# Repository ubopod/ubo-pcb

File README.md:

# Ubo PCBs

Open hardware design files for the printed circuit boards in the [Ubo Pod](https://getubo.com)
and its accessories — the main Raspberry Pi HAT, the side connector board, PCIe and M.2
adapters, a flex cable, and an NFC board. Sources are a mix of **Eagle CAD** and **KiCad**;
newer designs are KiCad.

<table>
  <tr>
    <td align="center" width="33%">
      <br>
      <sub><b><a href="boards/ubo-sideboard/">Sideboard</a></b><br>ports to the back panel</sub>
    </td>
    <td align="center" width="33%">
      <br>
      <sub><b><a href="boards/ubo-hab-v2/">HAB v2</a></b><br>PCIe, USB-C PD and PoE+</sub>
    </td>
    <td align="center" width="33%">
      <br>
      <sub><b><a href="boards/ubo-pcie-adapter/">PCIe adapter</a></b><br>M.2 M-key for the Pi 5</sub>
    </td>
  </tr>
  <tr>
    <td align="center">
      <br>
      <sub><b><a href="boards/m2-mkey-to-aekey/">M.2 M-key to A/E-key</a></b><br>runs a Google Coral</sub>
    </td>
    <td align="center">
      <br>
      <sub><b><a href="boards/pcie-fpc-s-shaped/">S-shaped PCIe FPC</a></b><br>2-layer flex cable</sub>
    </td>
    <td align="center">
      <br>
      <sub><b>As fabricated</b><br>a populated sideboard</sub>
    </td>
  </tr>
</table>

## Boards

Each board lives in its own directory under [`boards/`](boards/) with its own README.

| Board | Rev | Tool | Status | Connects to |
|---|---|---|---|---|
| [**ubo-top-hat**](boards/ubo-top-hat/) | v1.6 | Eagle | Production | Raspberry Pi 40-pin header |
| [**ubo-sideboard**](boards/ubo-sideboard/) | v1.5.2 | KiCad | Current | Pi 4/5 side ports + top HAT |
| ↳ [v1.4](boards/ubo-sideboard/v1.4-eagle/) | v1.4 | Eagle | Superseded by v1.5.2 | — |
| [**ubo-hab-v2**](boards/ubo-hab-v2/) | v4 | KiCad | Current | Raspberry Pi 5 PCIe + power |
| [**ubo-pcie-adapter**](boards/ubo-pcie-adapter/) | v3 | KiCad | Superseded by HAB v2 | Raspberry Pi 5 PCIe |
| [**m2-mkey-to-aekey**](boards/m2-mkey-to-aekey/) | — | KiCad | Built and tested | M.2 M-key slot |
| [**pcie-fpc-s-shaped**](boards/pcie-fpc-s-shaped/) | v2 | KiCad | Prototype, revision in progress | PCIe adapter FPC connectors |
| [**ubo-nfc-hat**](boards/ubo-nfc-hat/) | 1.0 | KiCad | Experimental | I²C via 1×8 headers |

**What each one is:**

- **ubo-top-hat** — the main Ubo board. LCD, keypad, RGB LED ring, WM8960 audio with speakers and
  microphones, IR transmit/receive, temperature and light sensors, EEPROM, fan, power button, and
  an experimental SDR section.
- **ubo-sideboard** — brings the Pi's mini HDMI, USB-C power, and audio jack around to the back of
  the enclosure, and adds a microSD extender, STEMMA Qt connectors, a power button, and a fan header.
- **ubo-hab-v2** — "hardware added on the bottom." PCIe to M.2 M-key, with optional USB-C PD and
  PoE+ power input modules and 12V/5V/3.3V breakouts.
- **ubo-pcie-adapter** — the first HAB revision; a simpler PCIe to M.2 M-key adapter.
- **m2-mkey-to-aekey** — adapts an M.2 M-key slot to A/E-key, so a Google Coral accelerator can go
  where an NVMe drive would.
- **pcie-fpc-s-shaped** — a 2-layer S-shaped FPC cable matching the connector positions on the
  PCIe adapter.
- **ubo-nfc-hat** — NTAG I²C plus NFC tag with a chain of addressable RGB LEDs.

## Repository layout

One directory per board. Within a board directory:

```
boards/<board>/
  README.md          documentation for this board
  <design files>     KiCad project or Eagle .sch/.brd at the top level,
                     or in a <rev>-<tool>/ subdirectory when a board has
                     more than one revision (see ubo-sideboard)
  images/            renders, layout screenshots, photos
  docs/              exported schematic and assembly PDFs
  datasheets/        datasheets for the components used on this board
  mechanical/        board outline DXF, STEP and other 3D models
```

Not every board has every subdirectory — they exist where there is something to put in them.

## Opening the files

- **KiCad projects** (`.kicad_pro`) — KiCad 8 or 9. Open the `.kicad_pro`, not the individual
  schematic or board files, so the project's library tables load.
- **Eagle designs** (`.sch` / `.brd`) — authored in Eagle CAD 9.6.2. KiCad can also import them
  via *File → Import → Non-KiCad Project*.

## License

Copyright © Ubo Pod.

These designs are licensed under the **CERN Open Hardware Licence Version 2 – Strongly
Reciprocal** (`CERN-OHL-S-2.0`). The full text is in [LICENSE](LICENSE).

In plain terms:

- **You can** use, study, modify, manufacture, and sell these boards, commercially or not.
- **If you distribute a modified design**, you have to release your modified source under this
  same licence, so the next person gets what you got.
- **If you sell or give away a product** made from these designs, you have to tell the recipient
  where to obtain the source for it.
- **There is no warranty.** These are hobbyist and small-batch designs; verify them yourself
  before committing to a fabrication run.

That summary is for orientation only — [LICENSE](LICENSE) is the document that actually governs.

To reuse a board here, keep the copyright and licence notices in the design files, and note your
own changes.

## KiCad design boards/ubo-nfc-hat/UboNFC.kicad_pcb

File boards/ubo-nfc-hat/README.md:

# Ubo NFC Hat

An NFC tag board with an addressable RGB LED ring, designed to attach to the Ubo Pod over I²C.
See the [repository index](../../README.md) for the other boards.

| | |
|---|---|
| **Revision** | 1.0 (schematic title block dated 2024-09-15) |
| **Tool** | KiCad — `UboNFC.kicad_pro` |
| **Stack-up** | 2 layers (F.Cu / B.Cu) |
| **Interface** | I²C + 1-wire LED data, via a pair of 1×8 headers |

## Attribution

This design is derived from **"Badge Tag NFC" by HXR.DK**, which is still named in the KiCad
schematic title block. The Ubo adaptation keeps the upstream NFC front-end and adds the LED
chain and the pass-through header arrangement described below.

> **TODO:** confirm the upstream project URL and its license, and record both here.

## Design

| Part | Function |
|---|---|
| **NXP NT3H2x11** (NTAG I²C plus) | NFC Forum Type 2 tag with an I²C interface, password protection, and energy harvesting. Readable by a phone over NFC *and* by the host over I²C. |
| **12 × SK6812SIDE-A** | Side-firing addressable RGB LEDs, daisy-chained from `LED_IN` through to `LED_OUT`. |
| **3 × SD103AW** | Schottky diodes on the LED data / signal lines. |
| **R1–R3, C1** | Pull-ups and decoupling. |

Named nets of interest: `COIL` and `VOUT` are the NFC antenna coil and the energy-harvesting
output; `FieldDetect` signals the host when an NFC field is present; `PushButton` brings a
button input out to the headers.

## Pinout

Two 1×8 horizontal headers. **J1** is the input side and **J2** carries the same signals back out
plus `LED_OUT`, so the LED chain and the I²C bus can be continued to a downstream board.

| Pin | J1 (in) | J2 (out) |
|---:|---|---|
| 1 | +5V | LED_OUT |
| 2 | +3V3 | PushButton |
| 3 | SDA | GND |
| 4 | SCL | GND |
| 5 | LED_IN | SCL |
| 6 | GND | SDA |
| 7 | FieldDetect | +3V3 |
| 8 | PushButton | +5V |

Note that J2 is **not** a straight-through mirror of J1 — the pin order differs. Check the
orientation of any cable you build against this table.

## Status

Experimental. There are no board renders, photos, or fabrication outputs in the repo yet, and
the design has not been documented as built or tested.

> **TODO:** confirm which Ubo board or connector J1 is intended to mate with, and whether the
> `FieldDetect` and `PushButton` lines are wired to specific host GPIOs.

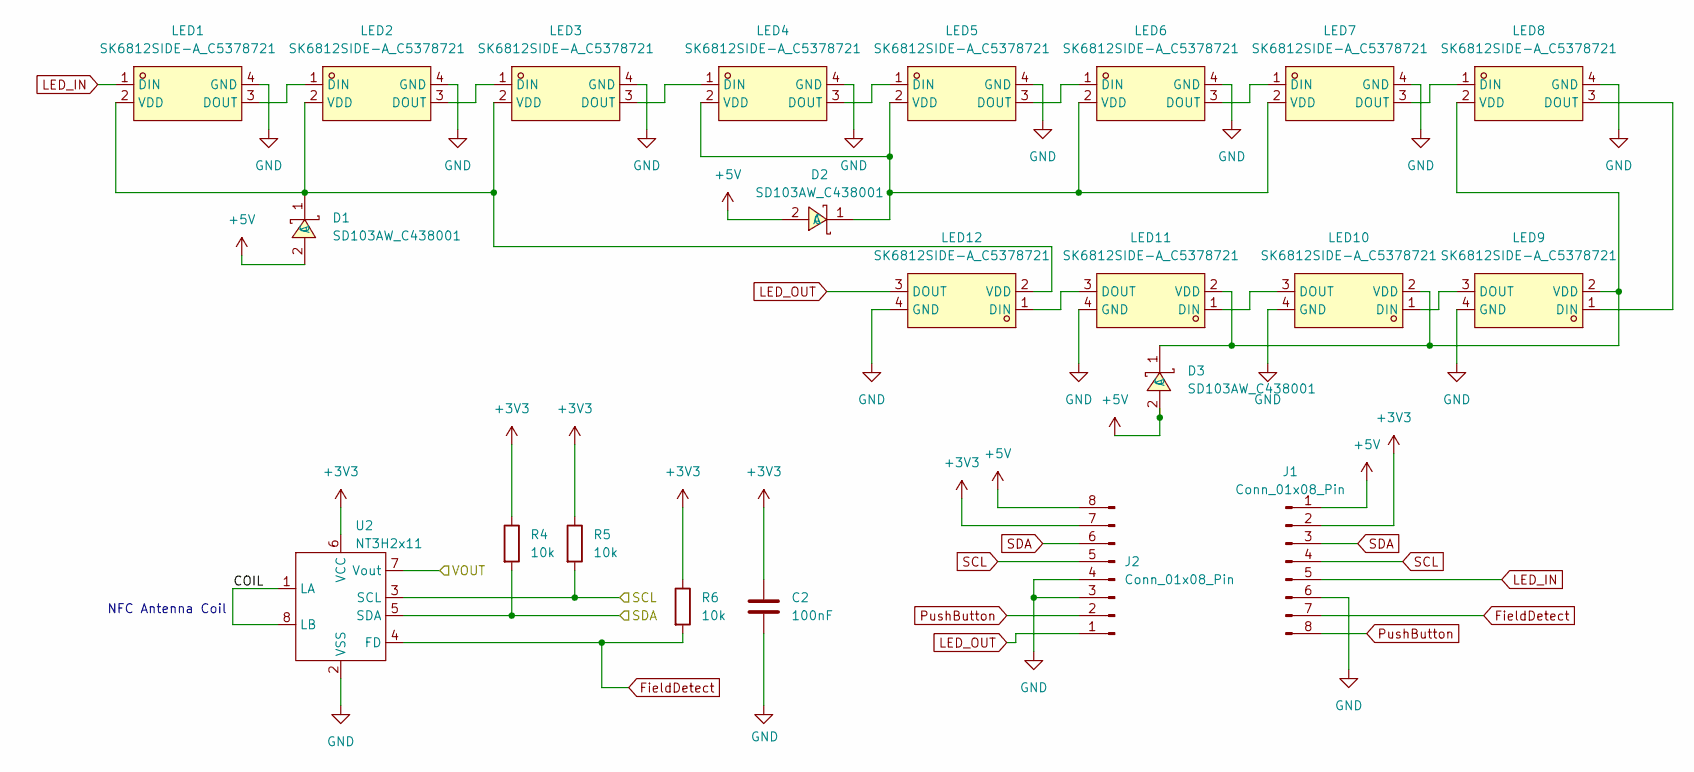
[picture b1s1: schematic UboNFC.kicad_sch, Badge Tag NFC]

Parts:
C2: 100nF; C_0603_1608Metric; LCSC C14663
D1, D2, D3: SD103AW_C438001; SOD-123_L2.7-W1.6-LS3.7-RD; LCSC Part C438001
J1, J2: Conn_01x08_Pin; PinHeader_1x08_P2.54mm_Horizontal
LED1, LED2, LED3, LED4, LED5, LED6, LED7, LED8, LED9, LED10, LED11, LED12: SK6812SIDE-A_C5378721; LED-SMD_4P-L4.0-W1.6-L; LCSC Part C5378721
R4, R5, R6: 10k; R_0603_1608Metric; LCSC C25804
U2: NT3H2x11; SO-8_3.9x4.9mm_P1.27mm; LCSC C2654822

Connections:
+3V3: C2.1, J1.2, J2.7, R4.1, R5.1, R6.1, U2.6 (VCC)
+5V: D1.2 (A), D2.2 (A), D3.2 (A), J1.1, J2.8
/COIL: U2.1 (LA), U2.8 (LB)
/VOUT: U2.7 (Vout)
FieldDetect: J1.7, R6.2, U2.4 (FD)
GND: C2.2, J1.6, J2.3, J2.4, LED1.4 (GND), LED2.4 (GND), LED3.4 (GND), LED4.4 (GND), LED5.4 (GND), LED6.4 (GND), LED7.4 (GND), LED8.4 (GND), LED9.4 (GND), LED10.4 (GND), LED11.4 (GND), LED12.4 (GND), U2.2 (VSS)
LED_IN: J1.5, LED1.1 (DIN)
LED_OUT: J2.1, LED12.3 (DOUT)
unnamed: D1.1 (C), LED1.2 (VDD), LED2.2 (VDD), LED3.2 (VDD), LED12.2 (VDD)
unnamed: D2.1 (C), LED4.2 (VDD), LED5.2 (VDD), LED6.2 (VDD), LED7.2 (VDD)
unnamed: D3.1 (C), LED8.2 (VDD), LED9.2 (VDD), LED10.2 (VDD), LED11.2 (VDD)
unnamed: LED1.3 (DOUT), LED2.1 (DIN)
unnamed: LED2.3 (DOUT), LED3.1 (DIN)
unnamed: LED3.3 (DOUT), LED4.1 (DIN)
unnamed: LED4.3 (DOUT), LED5.1 (DIN)
unnamed: LED5.3 (DOUT), LED6.1 (DIN)
unnamed: LED6.3 (DOUT), LED7.1 (DIN)
unnamed: LED7.3 (DOUT), LED8.1 (DIN)
unnamed: LED8.3 (DOUT), LED9.1 (DIN)
unnamed: LED9.3 (DOUT), LED10.1 (DIN)
unnamed: LED10.3 (DOUT), LED11.1 (DIN)
unnamed: LED11.3 (DOUT), LED12.1 (DIN)
PushButton: J1.8, J2.2
SCL: J1.4, J2.5, R5.2, U2.3 (SCL)
SDA: J1.3, J2.6, R4.2, U2.5 (SDA)

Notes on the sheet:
NFC Antenna Coil

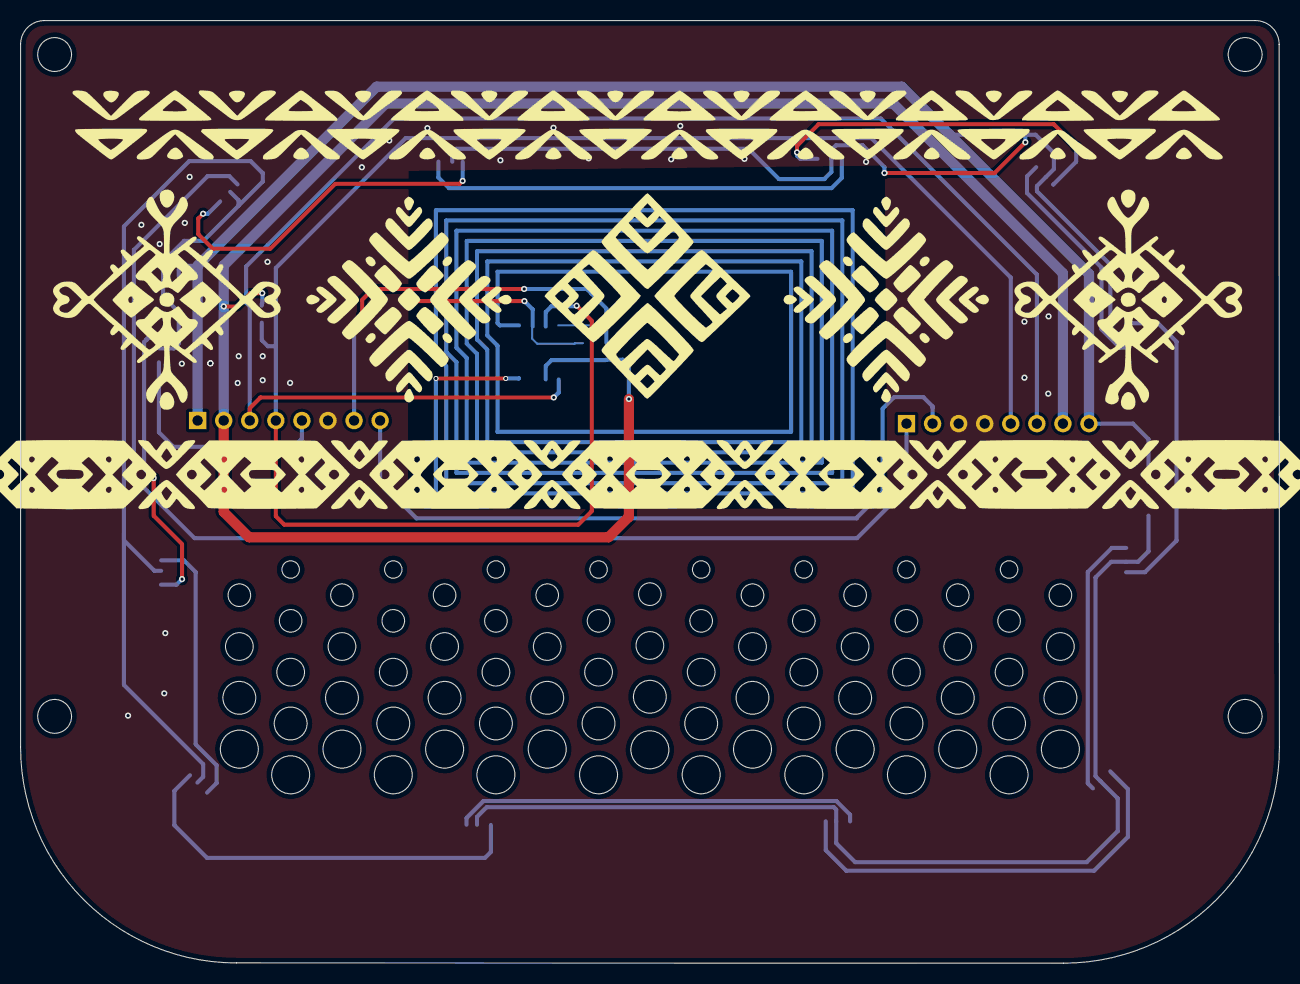
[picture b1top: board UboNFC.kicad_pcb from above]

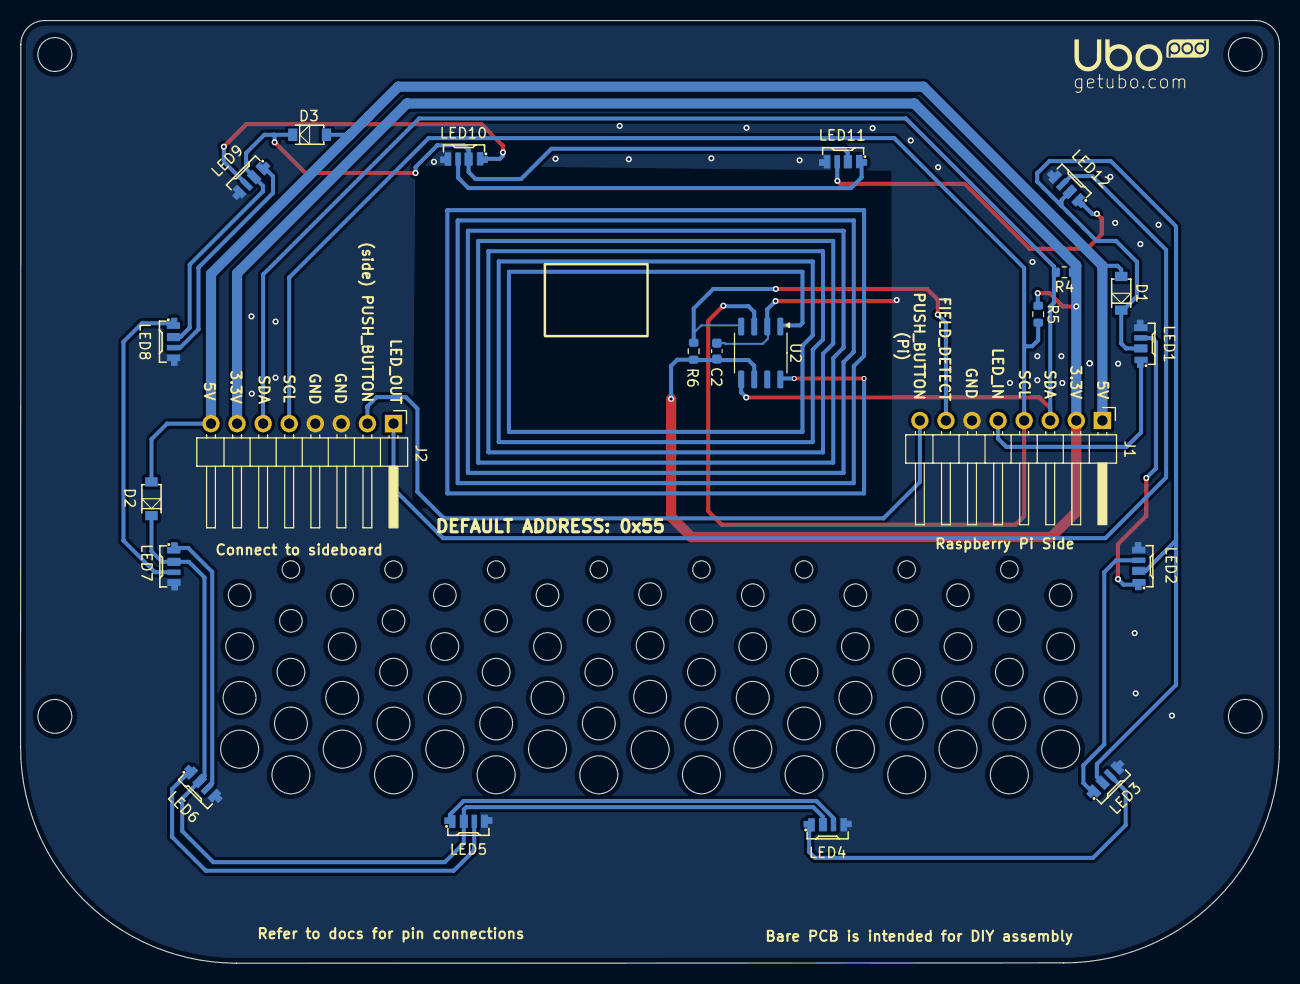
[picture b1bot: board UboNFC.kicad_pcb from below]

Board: 2 copper layers, 122.7 x 91.8 mm, 22 parts (22 on the bottom side), 24 nets.

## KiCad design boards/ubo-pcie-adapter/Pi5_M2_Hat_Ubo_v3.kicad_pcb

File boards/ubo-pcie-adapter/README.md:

# PCIe adapter board for Raspberry Pi 5

This board adds M.2 M-key connector to Raspberry Pi 5 and is compatible with Ubo Pod enclosure. You can use this to add NVMe drives to your Ubo Pod for faster and more reliable performance.

The design was inspired and enabled by George Smart – M1GEO design who reversed engineering PCIe connections of Raspberry Pi 5 before official documentations were released:

https://github.com/m1geo/Pi5_PCIe

<table>
  <tr>
    <td></td>
    <td></td>
  </tr>
</table>

The following images for the V1 of this adapter board. 

<table>
  <tr>
    <td></td>
    <td></td>
  </tr>
</table>

This design is used in [Ubo Pod](https://getubo.com) with a custom enclosure and quick access cover to reach NVMe drive or Google Coral accelerator. 

<table>
  <tr>
    <td></td>
    <td></td>
  </tr>
</table>

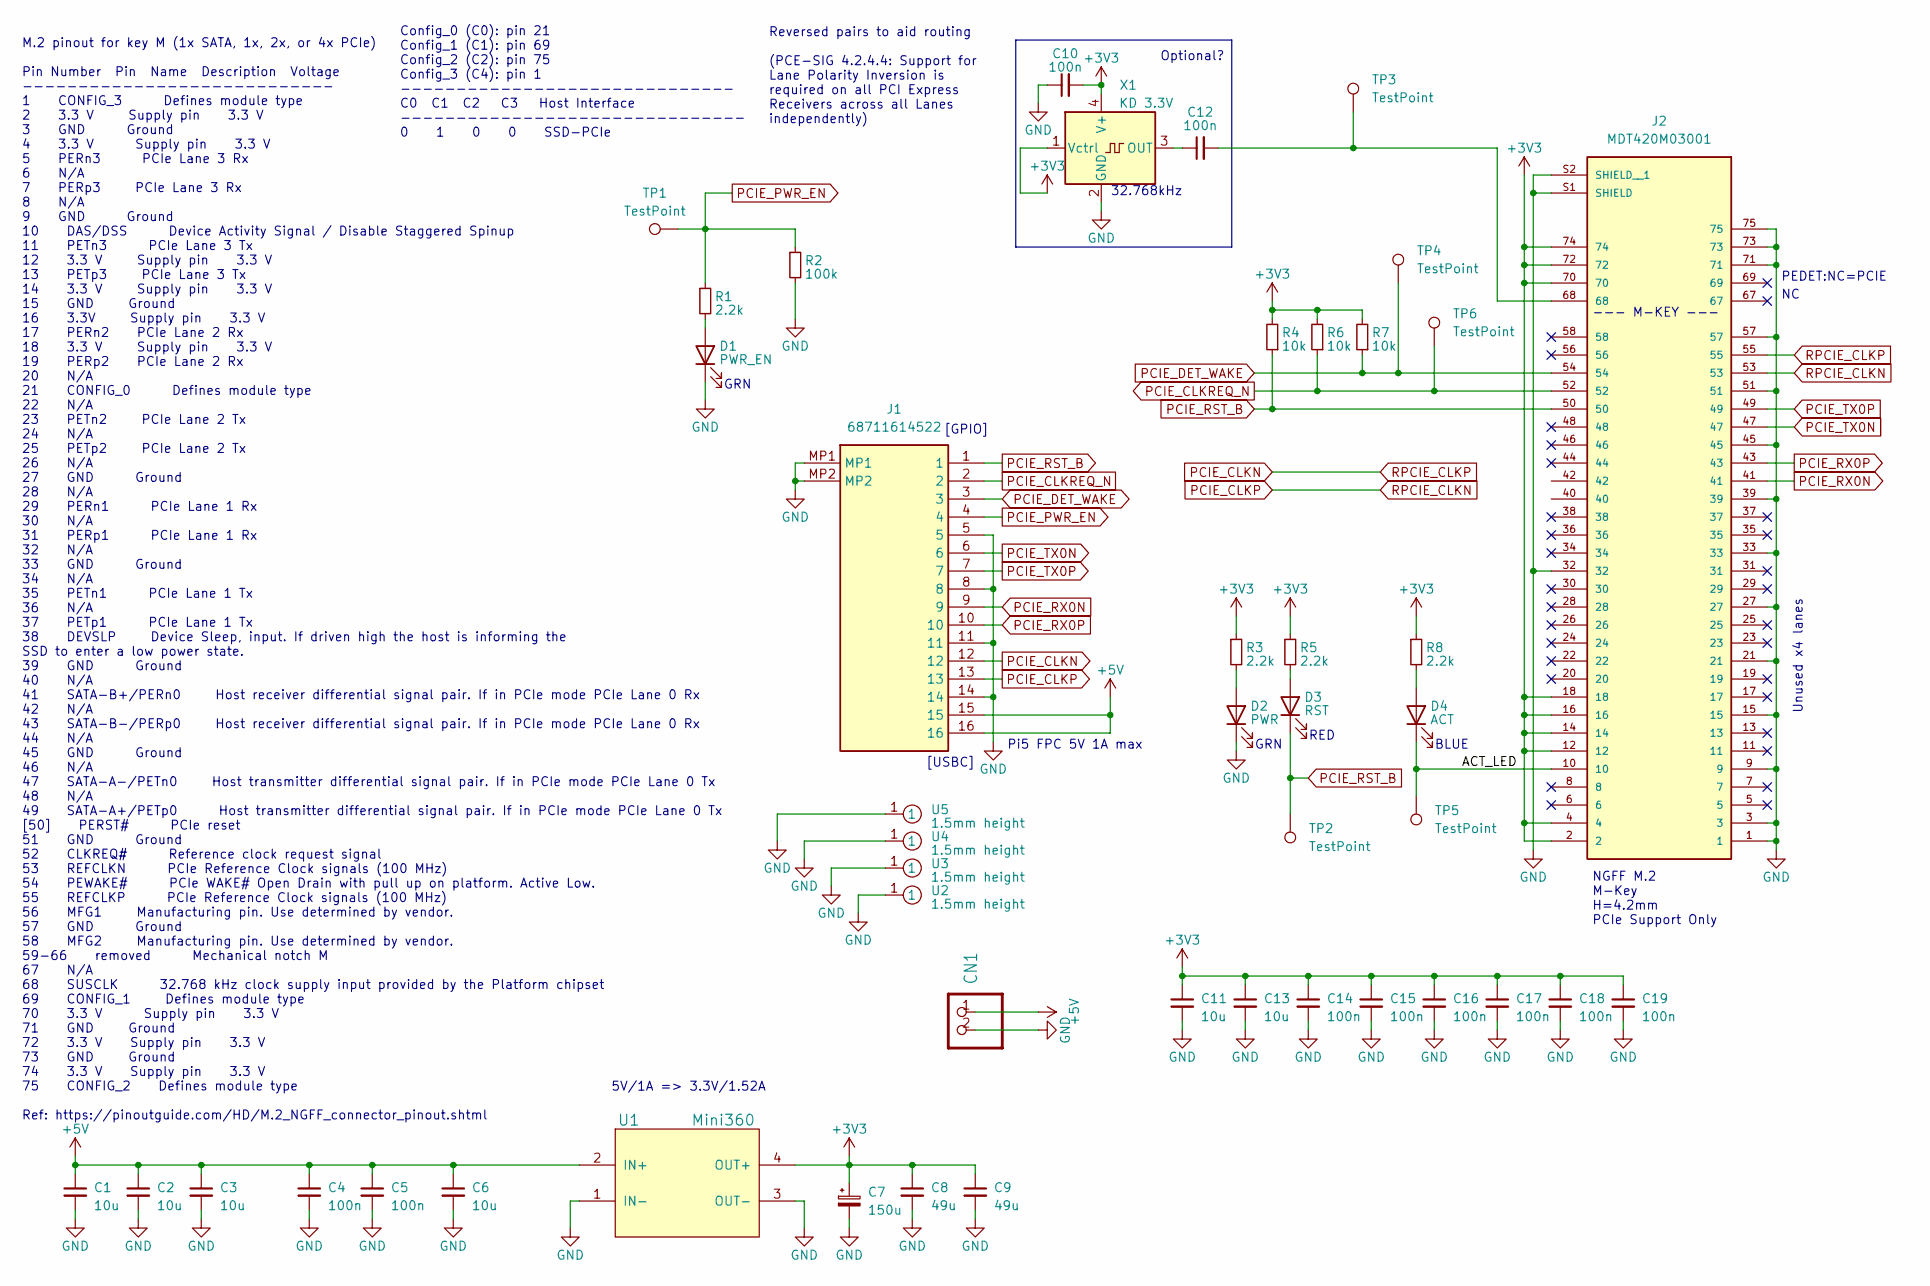
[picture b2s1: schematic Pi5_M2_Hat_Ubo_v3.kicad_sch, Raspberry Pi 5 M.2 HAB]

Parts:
C1, C2, C3, C6, C11, C13: 10u; C_0805_2012Metric_Pad1.18x1.45mm_HandSolder
C4, C5, C10, C12, C14, C15, C16, C17, C18, C19: 100n; C_0805_2012Metric_Pad1.18x1.45mm_HandSolder
C7: 150u; CP_Elec_6.3x7.7; LCSC C3032176
C8, C9: 49u; C_0805_2012Metric_Pad1.18x1.45mm_HandSolder
CN1: JST-PH-2-SMT_28380031
D1: PWR_EN; LED_0805_2012Metric_Pad1.15x1.40mm_HandSolder
D2: PWR; LED_0805_2012Metric_Pad1.15x1.40mm_HandSolder
D3: RST; LED_0805_2012Metric_Pad1.15x1.40mm_HandSolder
D4: ACT; LED_0805_2012Metric_Pad1.15x1.40mm_HandSolder
J1: 68711614522; Manufacturer_Part_Number 68711614522; Mouser Part Number 710-68711614522
J2: MDT420M03001; AMPHENOL_MDT420M03001
R1, R3, R5, R8: 2.2k; R_0805_2012Metric_Pad1.20x1.40mm_HandSolder
R2: 100k; R_0805_2012Metric_Pad1.20x1.40mm_HandSolder
R4, R6, R7: 10k; R_0805_2012Metric_Pad1.20x1.40mm_HandSolder
TP1, TP2, TP3, TP4, TP5, TP6: TestPoint; TestPoint_Pad_D1.5mm
U1: Mini360; Mini360_step-down
U2, U3, U4, U5: 1.5mm height; M2.5-nut
X1: KD 3.3V; Oscillator_SMD_Fordahl_DFAS15-4Pin_5.0x3.2mm

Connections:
+3V3: C7.1, C8.1, C9.1, C10.2, C11.1, C13.1, C14.1, C15.1, C16.1, C17.1, C18.1, C19.1, J2.2, J2.4, J2.12, J2.14, J2.16, J2.18, J2.70, J2.72, J2.74, R3.1, R4.2, R5.1, R6.2, R7.2, R8.1, U1.4 (OUT+), X1.1 (Vctrl), X1.4 (V+)
+5V: C1.1, C2.1, C3.1, C4.1, C5.1, C6.1, CN1.1 (2), J1.15, J1.16, U1.2 (IN+)
/ACT_LED: D4.1 (K), J2.10, TP5.1
GND: C1.2, C2.2, C3.2, C4.2, C5.2, C6.2, C7.2, C8.2, C9.2, C10.1, C11.2, C13.2, C14.2, C15.2, C16.2, C17.2, C18.2, C19.2, CN1.2 (1), D1.1 (K), D2.1 (K), J1.5, J1.8, J1.11, J1.14, J1.MP1, J1.MP2, J2.1, J2.3, J2.9, J2.15, J2.21, J2.27, J2.32, J2.33, J2.39, J2.45, J2.51, J2.57, J2.71, J2.73, J2.75, J2.S1 (SHIELD), J2.S2 (SHIELD__1), R2.2, U1.1 (IN-), U1.3 (OUT-), U2.1, U3.1, U4.1, U5.1, X1.2 (GND)
unnamed: C12.2, J2.68, TP3.1
unnamed: D1.2 (A), R1.2
unnamed: D2.2 (A), R3.2
unnamed: D3.2 (A), R5.2
unnamed: D4.2 (A), R8.2
unnamed: C12.1, X1.3 (OUT)
PCIE_CLKN: J1.12, J2.55
PCIE_CLKP: J1.13, J2.53
PCIE_CLKREQ_N: J1.2, J2.52, R6.1, TP6.1
PCIE_DET_WAKE: J1.3, J2.54, R7.1, TP4.1
PCIE_PWR_EN: J1.4, R1.1, R2.1, TP1.1
PCIE_RST_B: D3.1 (K), J1.1, J2.50, R4.1, TP2.1
PCIE_RX0N: J1.9, J2.41
PCIE_RX0P: J1.10, J2.43
PCIE_TX0N: J1.6, J2.47
PCIE_TX0P: J1.7, J2.49

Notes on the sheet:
PEDET:NC=PCIE
BLUE
RED
GRN
M.2 pinout for key M (1x SATA, 1x, 2x, or 4x PCIe) Pin Number Pin Name Description Voltage ---------------------------- 1 CONFIG_3 Defines module type 2 3.3 V Supply pin 3.3 V 3 GND Ground 4 3.3 V Supply pin 3.3 V 5 PERn3 PCIe Lane 3 Rx 6 N/A 7 PERp3 PCIe Lane 3 Rx 8 N/A 9 GND Ground 10 DAS/DSS Dev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
Config_0 (C0): pin 21 Config_1 (C1): pin 69 Config_2 (C2): pin 75 Config_3 (C4): pin 1 ------------------------------ C0 C1 C2 C3 Host Interface ------------------------------- 0 1 0 0 SSD-PCIe
[USBC]
--- M-KEY ---
32.768kHz
Optional?
Unused x4 lanes
Pi5 FPC 5V 1A max
Reversed pairs to aid routing (PCE-SIG 4.2.4.4: Support for Lane Polarity Inversion is required on all PCI Express Receivers across all Lanes independently)
NGFF M.2 M-Key H=4.2mm PCIe Support Only
[GPIO]
5V/1A => 3.3V/1.52A

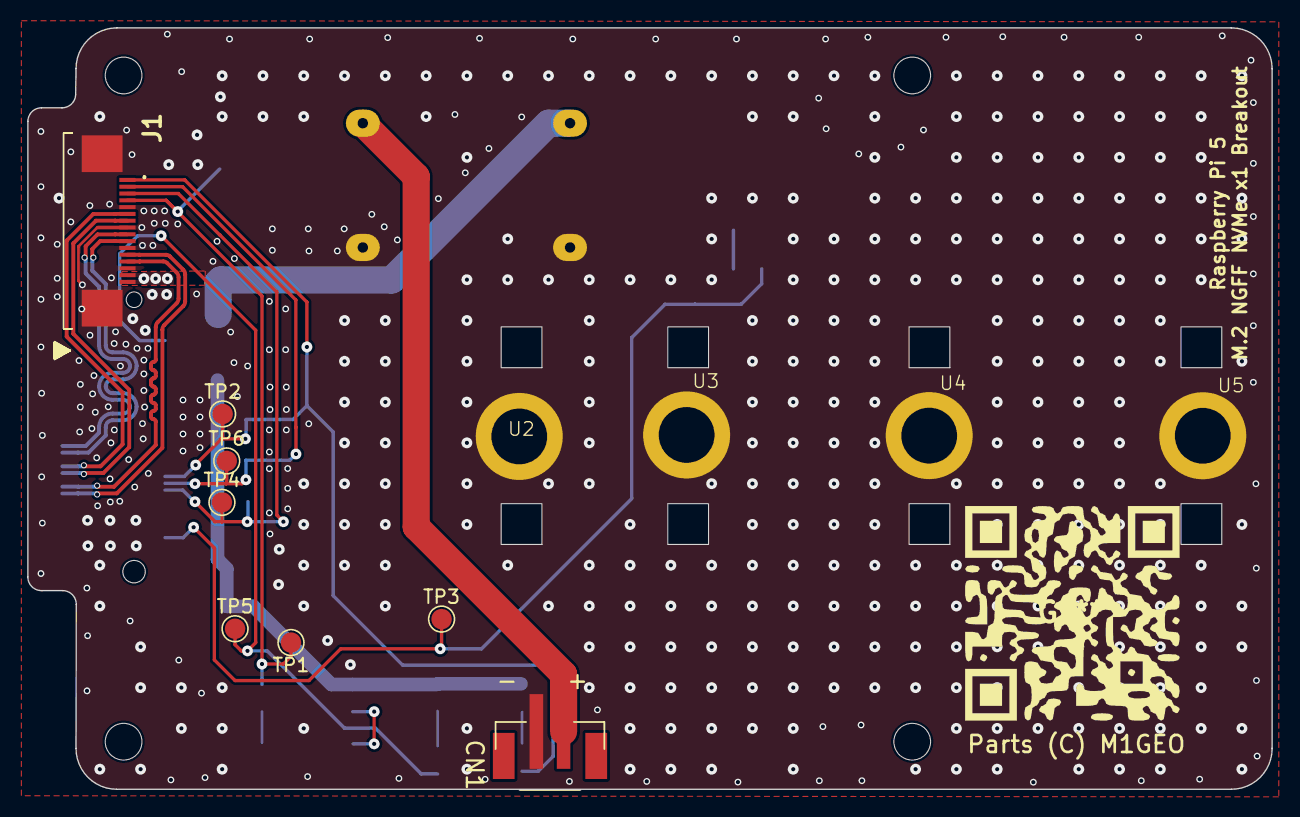
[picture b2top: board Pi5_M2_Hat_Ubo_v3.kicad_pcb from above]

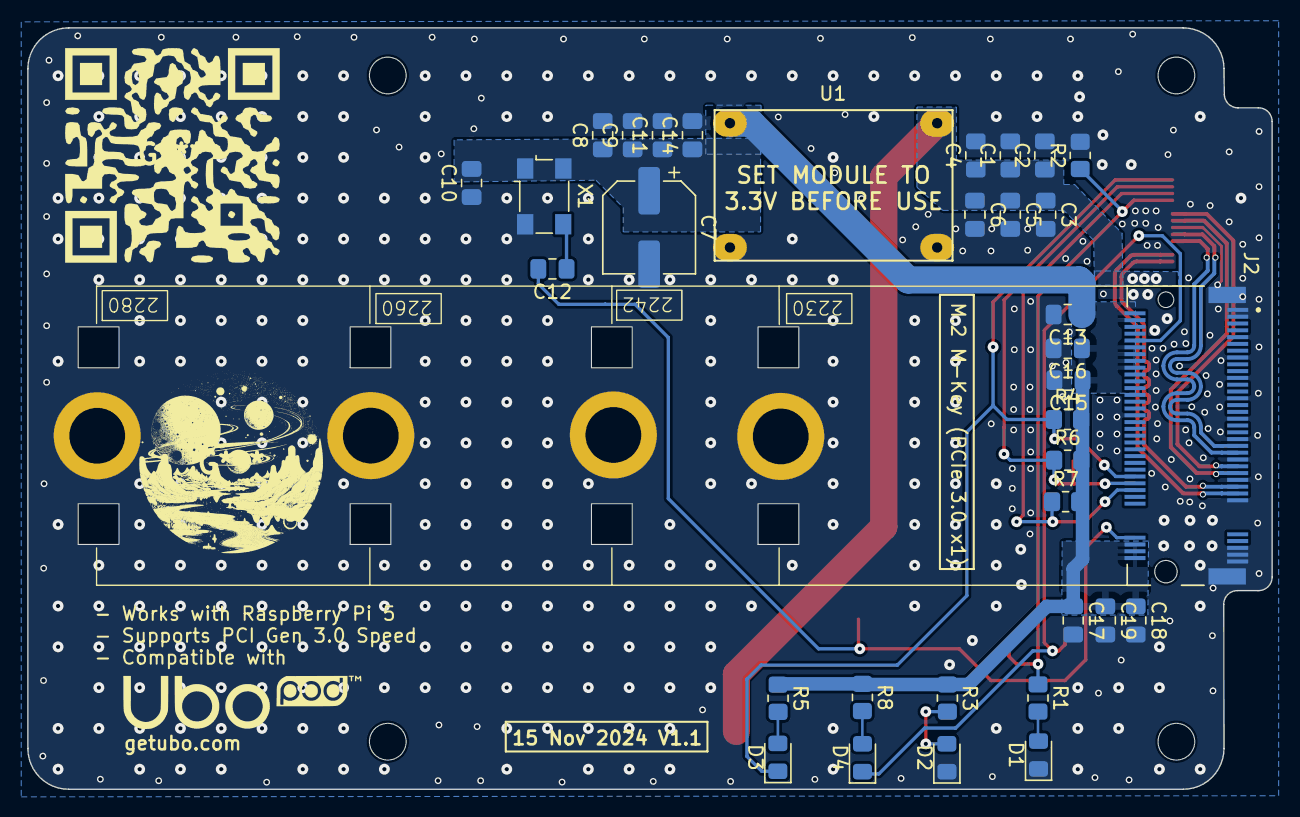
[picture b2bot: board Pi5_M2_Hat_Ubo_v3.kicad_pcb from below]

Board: 4 copper layers, 91.5 x 56.0 mm, 50 parts (34 on the bottom side), 20 nets.

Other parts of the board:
MH1, MH2, MH3, MH4: MountingHole_2.7mm_M2.5

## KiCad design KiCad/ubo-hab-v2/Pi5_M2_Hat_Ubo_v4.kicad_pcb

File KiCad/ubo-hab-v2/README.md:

# Ubo HAB - PCIe/USB-C/POE+ adapter board for Raspberry Pi 5

This is a update to [Ubo PCIe HAB v1](https://github.com/ubopod/ubo-pcb/tree/main/KiCad/ubo-pcie-adapter) with several design enhancement and features:

<table>
  <tr>
    <td></td>
    <td></td>
  </tr>
</table>

1. PCIe to M.2 M-key adapter with SMD round screw nuts (support 2230/2242/2260/2280)
2. Support high wattage peripherals and drives (~15W)
3. Power pogo pins to either receive additional power from Raspberry Pi and power up the Pi via HAB (see power in options below)
4. DIY upgrade possible purchasing MINI560, USB-PD, POE+ modules separately
5. HAB can be powered via 
  + An optional USB-C PD module/add-on at 12v/3A (or 19v/3A)
  + An optional POE module/add-on  
6. Power output breakouts
  + 12V output breakout 
  + 5V output breakout 
  + 3.3V output breakout 

## Purchasing

I am planning to make a small batch of these boards and if you are interested in purchasing one, you can
make a reservation on my shopify store for $1 to help me better estimate how many units I should be ordering.

The base model (no USB-PD, 5V buck converter, and pin headers assembled) will be probebly priced around $20~$25. 

The fully populated model (USB-PD, 5V buck converter, all pin headers assembled) will be cost probably around $35~$40.

POE+ modules will be sold separately at around $20.

## Power modules

Power modules can be bought from Amazon or Aliexpress. The 3.3V and 5V modules used in the design are known as 
MINI560 modules and can provide up to 5A of output current. They also have castellated pads that made DIY soldering
a breeze. 

+ USB-C PD 12V module on Amazon ([long format](https://www.amazon.com/dp/B09P8HGL9Y?th=1), [short format](https://www.amazon.com/dp/B0C7JTS26B?th=1))
+ Mini360 5V/3.3V step-down converter module on [Amazon](https://www.amazon.com/UMLIFE-mini560-Converter5A-Adjustable-Regulator/dp/B098J269QB?th=1)

<table>
  <tr>
    <td></td>
    <td></td>
    <td></td>
  </tr>
</table>

## POE module

The HAB (Hardware added on the bottom) breaks out POE input pins and 12V return voltage from the POE module. 
The module can be purchased an connected separately using jumber wires to the exposed headers. 
The image below shows an example of such POE module. I am working to source some good quality modules and make them
available for purchase on my personal shopify page.

<table>
  <tr>
    <td></td>
  </tr>
</table>

This design can be used in [Ubo Pod](https://getubo.com) with a custom enclosure and quick access cover to reach NVMe drive or Google Coral accelerator.

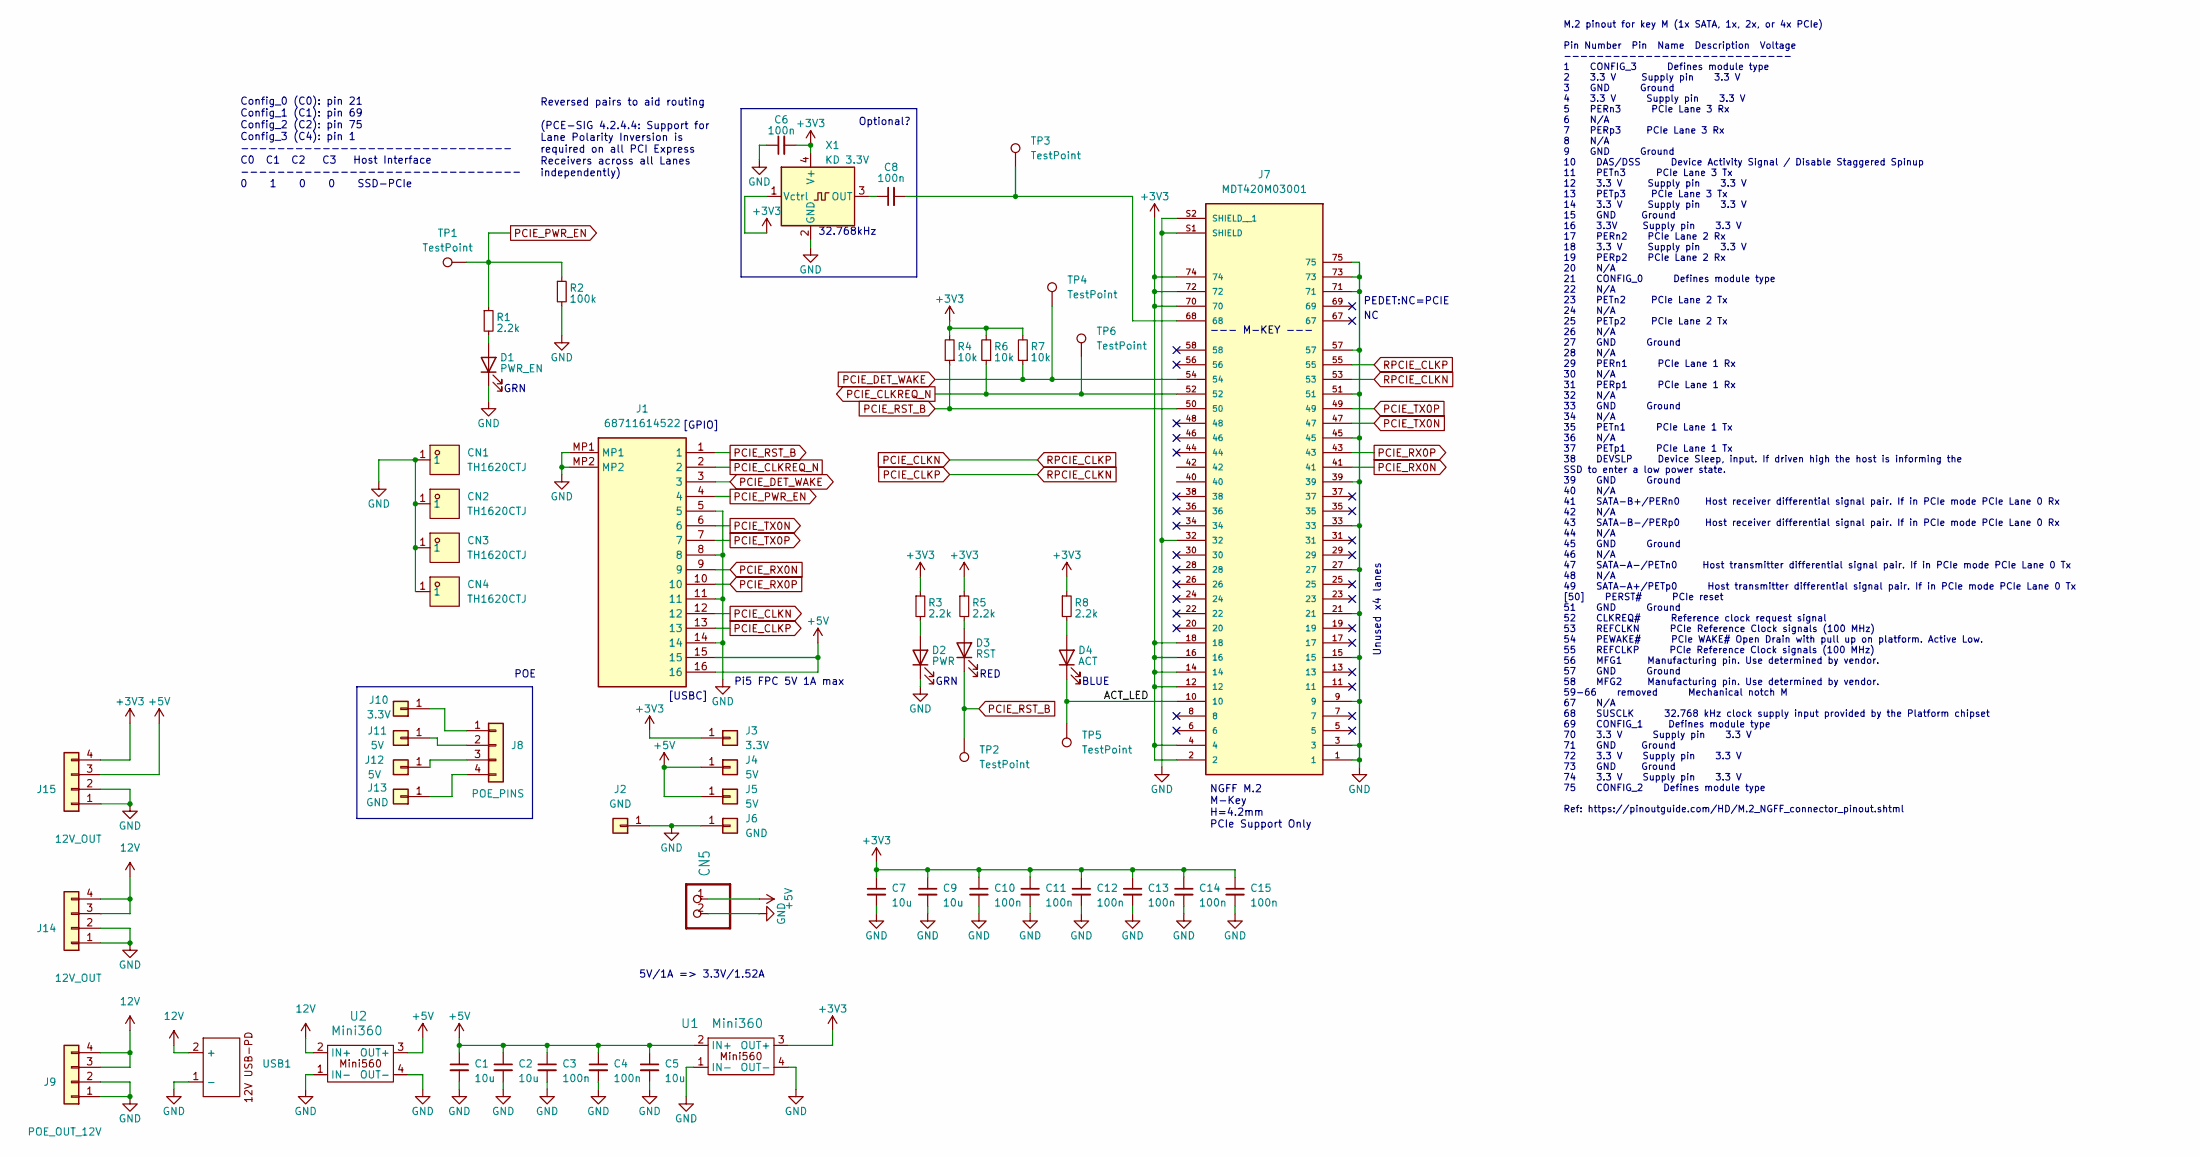
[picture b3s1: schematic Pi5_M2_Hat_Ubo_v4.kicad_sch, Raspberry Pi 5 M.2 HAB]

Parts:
C1, C2, C5, C7, C9: 10u; C_0805_2012Metric_Pad1.18x1.45mm_HandSolder; LCSC C15850
C3, C4, C6, C8, C10, C11, C12, C13, C14, C15: 100n; C_0805_2012Metric_Pad1.18x1.45mm_HandSolder; LCSC C28233
CN1, CN2, CN3, CN4: TH1620CTJ; SMD_BD4.0-D2.5; LCSC Part C3020123
CN5: CONN-SMD_P2.00_S2B-PH-SM4-TB-LF-SN; LCSC C295747
D1: PWR_EN; LED_0805_2012Metric_Pad1.15x1.40mm_HandSolder; LCSC C2297
D2: PWR; LED_0805_2012Metric_Pad1.15x1.40mm_HandSolder; LCSC C2297
D3: RST; LED_0805_2012Metric_Pad1.15x1.40mm_HandSolder; LCSC C84256
D4: ACT; LED_0805_2012Metric_Pad1.15x1.40mm_HandSolder; LCSC C2293
J1: 68711614522; Manufacturer_Part_Number 68711614522; Mouser Part Number 710-68711614522
J2, J6, J13: GND; Pogopin; LCSC C7471676
J3, J10: 3.3V; Pogopin; LCSC C7471676
J4, J5, J11, J12: 5V; Pogopin; LCSC C7471676
J7: MDT420M03001; AMPHENOL_MDT420M03001; LCSC C2832351
J8: POE_PINS; PinHeader_1x04_P2.54mm_Horizontal
J9: POE_OUT_12V; PinHeader_1x04_P2.54mm_Horizontal
J14, J15: 12V_OUT; PinHeader_2x02_P2.54mm_Horizontal
R1, R3, R5, R8: 2.2k; R_0805_2012Metric_Pad1.20x1.40mm_HandSolder; LCSC C17520
R2: 100k; R_0805_2012Metric_Pad1.20x1.40mm_HandSolder; LCSC C149504
R4, R6, R7: 10k; R_0805_2012Metric_Pad1.20x1.40mm_HandSolder; LCSC C17414
TP1, TP2, TP3, TP4, TP5, TP6: TestPoint; TestPoint_Pad_D1.5mm
U1, U2: Mini360; mini560
USB1: USB-PD-MODULE
X1: KD 3.3V; Oscillator_SMD_Fordahl_DFAS15-4Pin_5.0x3.2mm

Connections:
12V: J9.3, J9.4, J14.3, J14.4, U2.2 (IN+), USB1.2 (+)
+3V3: C6.2, C7.1, C9.1, C10.1, C11.1, C12.1, C13.1, C14.1, C15.1, J3.1, J7.2, J7.4, J7.12, J7.14, J7.16, J7.18, J7.70, J7.72, J7.74, J15.4, R3.1, R4.2, R5.1, R6.2, R7.2, R8.1, U1.3 (OUT+), X1.1 (Vctrl), X1.4 (V+)
+5V: C1.1, C2.1, C3.1, C4.1, C5.1, CN5.1 (2), J1.15, J1.16, J4.1, J5.1, J15.3, U1.2 (IN+), U2.3 (OUT+)
/ACT_LED: D4.1 (K), J7.10, TP5.1
GND: C1.2, C2.2, C3.2, C4.2, C5.2, C6.1, C7.2, C9.2, C10.2, C11.2, C12.2, C13.2, C14.2, C15.2, CN1.1, CN2.1, CN3.1, CN4.1, CN5.2 (1), D1.1 (K), D2.1 (K), J1.5, J1.8, J1.11, J1.14, J1.MP1, J1.MP2, J2.1, J6.1, J7.1, J7.3, J7.9, J7.15, J7.21, J7.27, J7.32, J7.33, J7.39, J7.45, J7.51, J7.57, J7.71, J7.73, J7.75, J7.S1 (SHIELD), J7.S2 (SHIELD__1), J9.1, J9.2, J14.1, J14.2, J15.1, J15.2, R2.2, U1.1 (IN-), U1.4 (OUT-), U2.1 (IN-), U2.4 (OUT-), USB1.1 (-), X1.2 (GND)
unnamed: C8.2, J7.68, TP3.1
unnamed: D1.2 (A), R1.2
unnamed: D2.2 (A), R3.2
unnamed: D3.2 (A), R5.2
unnamed: D4.2 (A), R8.2
unnamed: J8.1, J10.1
unnamed: J8.2, J11.1
unnamed: J8.3, J12.1
unnamed: J8.4, J13.1
unnamed: C8.1, X1.3 (OUT)
PCIE_CLKN: J1.12, J7.55
PCIE_CLKP: J1.13, J7.53
PCIE_CLKREQ_N: J1.2, J7.52, R6.1, TP6.1
PCIE_DET_WAKE: J1.3, J7.54, R7.1, TP4.1
PCIE_PWR_EN: J1.4, R1.1, R2.1, TP1.1
PCIE_RST_B: D3.1 (K), J1.1, J7.50, R4.1, TP2.1
PCIE_RX0N: J1.9, J7.41
PCIE_RX0P: J1.10, J7.43
PCIE_TX0N: J1.6, J7.47
PCIE_TX0P: J1.7, J7.49

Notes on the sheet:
PEDET:NC=PCIE
BLUE
RED
GRN
M.2 pinout for key M (1x SATA, 1x, 2x, or 4x PCIe) Pin Number Pin Name Description Voltage ---------------------------- 1 CONFIG_3 Defines module type 2 3.3 V Supply pin 3.3 V 3 GND Ground 4 3.3 V Supply pin 3.3 V 5 PERn3 PCIe Lane 3 Rx 6 N/A 7 PERp3 PCIe Lane 3 Rx 8 N/A 9 GND Ground 10 DAS/DSS Dev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
Config_0 (C0): pin 21 Config_1 (C1): pin 69 Config_2 (C2): pin 75 Config_3 (C4): pin 1 ------------------------------ C0 C1 C2 C3 Host Interface ------------------------------- 0 1 0 0 SSD-PCIe
[USBC]
--- M-KEY ---
POE
32.768kHz
Optional?
Unused x4 lanes
Pi5 FPC 5V 1A max
Reversed pairs to aid routing (PCE-SIG 4.2.4.4: Support for Lane Polarity Inversion is required on all PCI Express Receivers across all Lanes independently)
NGFF M.2 M-Key H=4.2mm PCIe Support Only
[GPIO]
5V/1A => 3.3V/1.52A

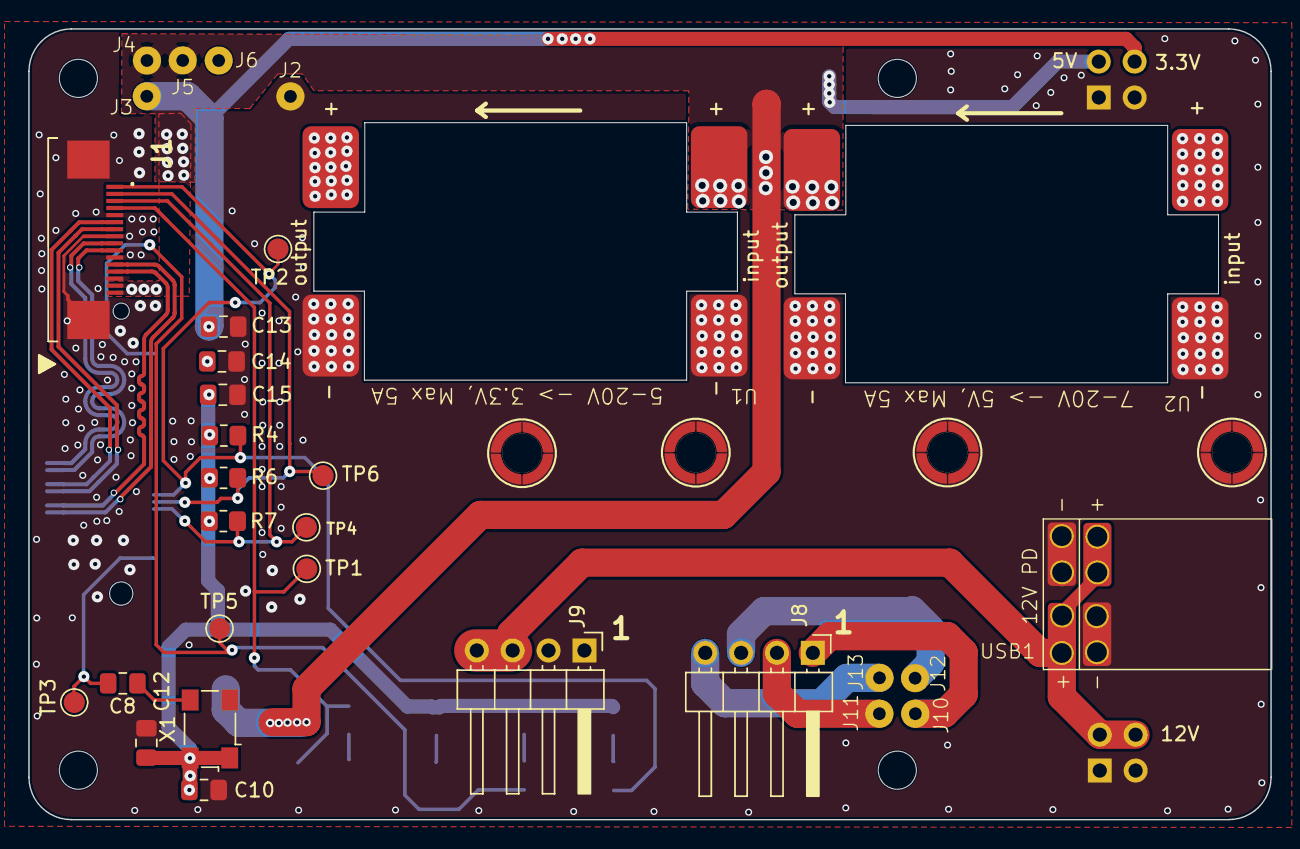
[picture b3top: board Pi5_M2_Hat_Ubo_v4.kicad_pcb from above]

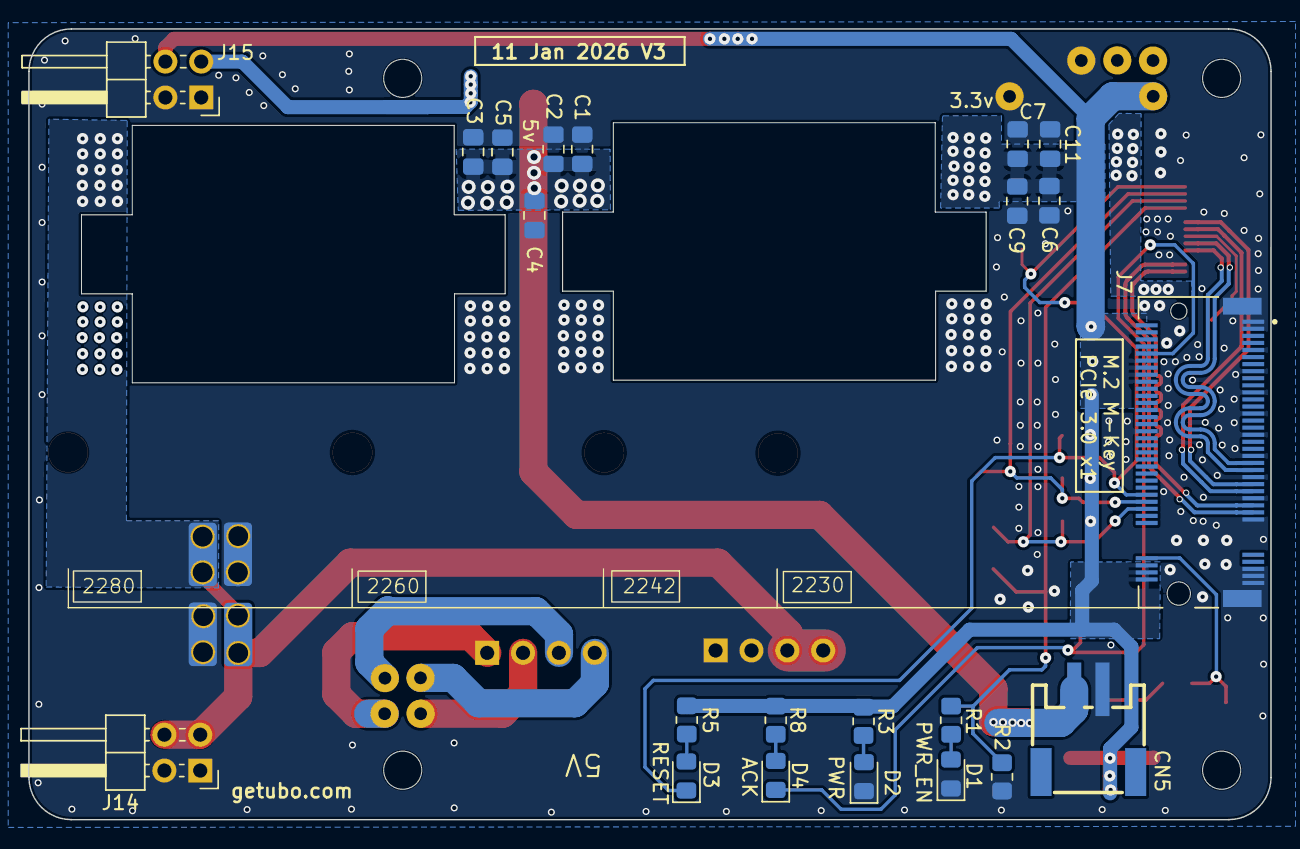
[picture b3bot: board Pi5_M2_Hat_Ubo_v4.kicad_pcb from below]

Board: 4 copper layers, 88.0 x 56.0 mm, 61 parts (22 on the bottom side), 25 nets.

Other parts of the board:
MH1, MH2, MH3, MH4: MountingHole_2.7mm_M2.5

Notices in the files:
boards/ubo-nfc-hat/UboNFC.kicad_pcb:
CC-BY-SA
